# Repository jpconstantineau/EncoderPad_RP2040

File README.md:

# EncoderPad RP2040

### What is the EncoderPad RP2040?

The EncoderPad RP2040 is a Video Editing Macropad with a 60mm Encoder Wheel. This encoder is made of metal and feels like it will last forever. The EncoderPad uses 9 mechanical switches (Cherry MX type).  The keys are hot-swap socketed and have an individual underglow RGB LED which can be turned on.

### How do I build it?

You don't need many tools to build it!  
* Install the rotary encoder on the top plate. (there are nuts at the back)
* Press the switches through the top plate
* Align the key switch pins with their sockets and press them in, 
* Attach the wires for the rotary encoder
* Screw in the top/bottom screws through the standoffs
* Install the keycaps
* Install the adhesive rubber bump ons as feet.

### How do I program it?

The Encoder Pad can be programmed with CircuitPython.  To get started, get the latest download from the official [CircuitPython.org](https://circuitpython.org/) site, put the RP2040 in  booloader mode by pressing "reset" while pressing the "boot" button and drag/drop in the UF2 file you just downloaded. You are now ready to program it! No build tools required on your computer!

Notes: 
* CircuitPython is licensed under the [MIT License](https://github.com/adafruit/circuitpython/blob/main/LICENSE).
* Default Firmware for the EncoderPad is based on the [MACROPAD Hoykeys](https://learn.adafruit.com/macropad-hotkeys) example for the [Adafruit Macropad RP2040](https://learn.adafruit.com/adafruit-macropad-rp2040) which is part of the [Adafruit Learning System Guides](https://learn.adafruit.com/), licensed under the [MIT License](https://github.com/adafruit/Adafruit_Learning_System_Guides/blob/main/LICENSE).
* Default firmware is **MIT** licensed.

### Hardware License

Design of the EncoderPad_RP2040 is licensed under **CERN Open Hardware Licence Version 2 - Weakly Reciprocal**

See license.txt for more details. See this [FAQ](https://ohwr.org/project/cernohl/wikis/faq#q-copyright-does-not-cover-hardware-how-do-you-implement-strongly-reciprocal-licensing-in-cern-ohl-s) for more information on this license.

### Licenses from reference material and libraries

|  Item  | Description | Source  | License  |
|----|----      | :-----  | :-------- |
| RP2040 Hardware Design Guide  | RP2040 Documentation (for reference) | [link](https://datasheets.raspberrypi.org/rp2040/hardware-design-with-rp2040.pdf) | CC BY-ND |
| RP2040 Minimal Design Example | Kicad Project | [link](https://datasheets.raspberrypi.org/rp2040/Minimal-KiCAD.zip) | 3-Clause BSD (considered as source code included as part of documentation) |
| kicad libraries | Core libraries from Kicad | [link](https://www.kicad.org/libraries/license/) | CC-BY-SA 4.0 (with exception)|
| kicad libraries | switch symbols and footprints | [link](https://github.com/sszczep/kicad-libraries)| MIT | 

### openmoko-usb-oui application details

[USB PID Request](https://github.com/openmoko/openmoko-usb-oui)

1. (done) Have a README[.txt|.md] file describing which part is under which license this will help to quickly identify the project's license, particularly when several licenses are combined, or your are using libraries under other licenses. Also make sure the combination is allowed by the individual licenses.
2. (done) Include all full text licenses in a LICENSE[.txt] file
3. (done) Include a copyright notice in the schematic sheet(s), including author and date this will determine who the copyright holder is, and when the copyright will expire.
4. (done) Include the license name in the schematic sheet(s) this becomes important when different license are combined, and parts of the project, or libraries, are under different licenses
5. (done) Include all schematic symbols and board footprint libraries in the project without that the project can't be seen as complete. Also ensure their license is compatible.
66. (done) Export the schematic capture as pdf, and board layout as gerber+NC drill [and other fabrication output] files - not every user can, or wants, to install the EDA suite you are using. This is even more important if in the future this suite stops supporting the current format. If you don't want to mix the fabrication output with the source files, have a general project page pointing to the source files and fabrication output.

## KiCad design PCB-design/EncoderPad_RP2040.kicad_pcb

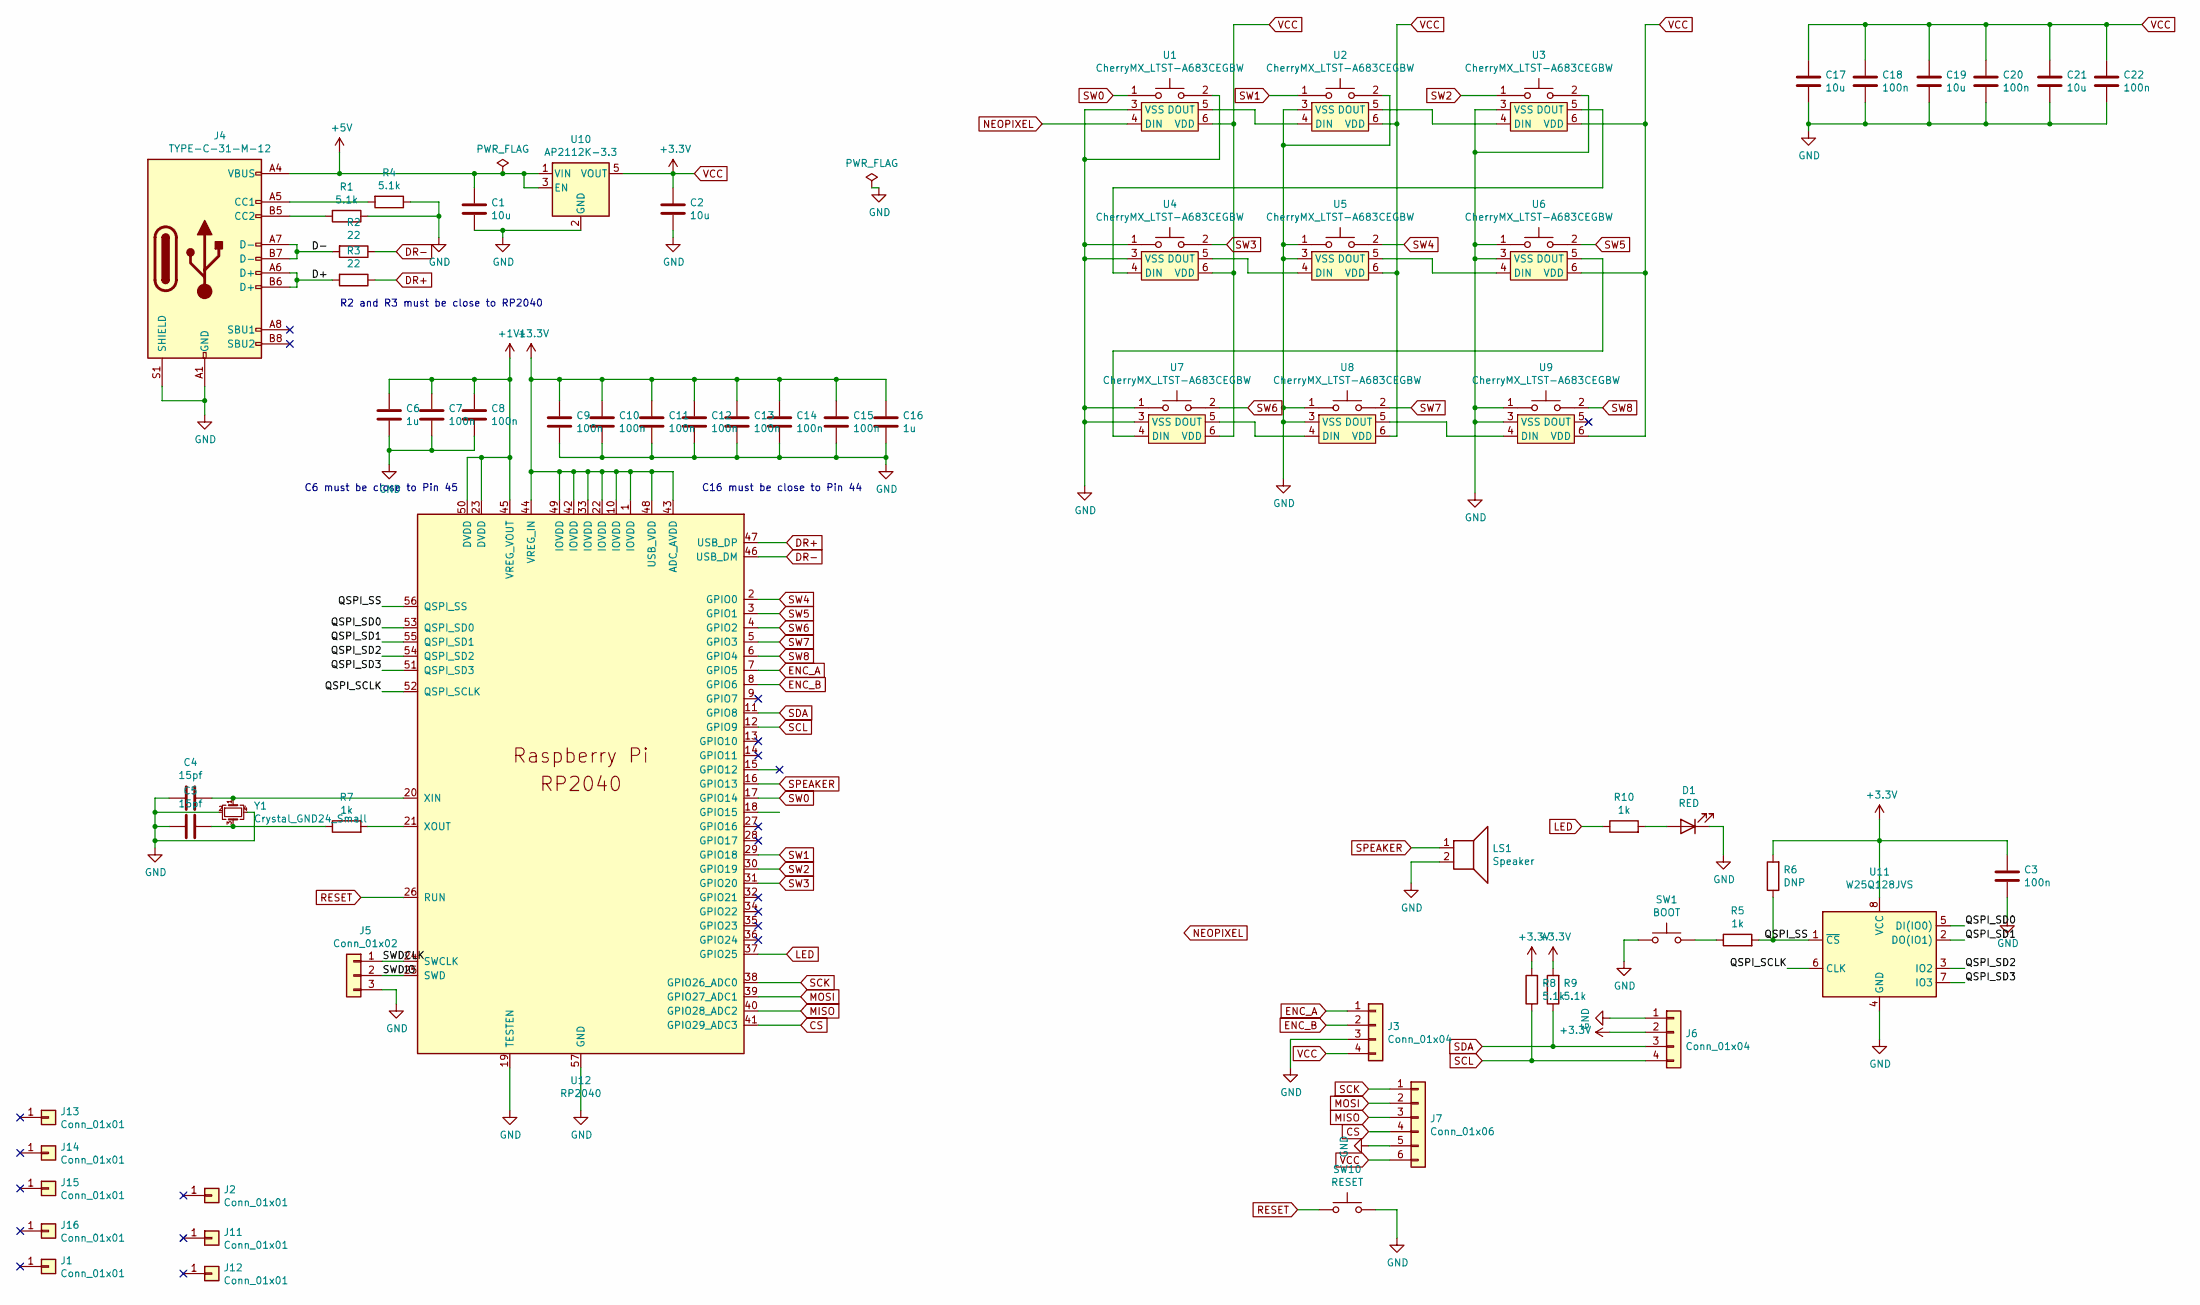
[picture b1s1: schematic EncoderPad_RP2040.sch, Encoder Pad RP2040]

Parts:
C1, C2, C17, C19, C21: 10u; C_0603_1608Metric; LCSC C15850
C3, C7, C8, C9, C10, C11, C12, C13, C14, C15, C18, C20, C22: 100n; C_0603_1608Metric; LCSC C14663
C4, C5: 15pf; C_0603_1608Metric; LCSC C1644
C6, C16: 1u; C_0603_1608Metric; LCSC C15849
D1: RED; LED_0603_1608Metric
J1: Conn_01x01; CNC_Encoder
J2, J11, J12, J13, J14, J15, J16: Conn_01x01; MountingHole_3.5mm
J3: Conn_01x04; PinHeader_1x04_P2.54mm_Horizontal
J4: TYPE-C-31-M-12; USB_C_Receptacle_HRO_TYPE-C-31-M-12; LCSC C165948
J5: Conn_01x02; PinHeader_1x03_P2.54mm_Vertical
J6: Conn_01x04; PinHeader_1x04_P2.54mm_Vertical
J7: Conn_01x06; PinHeader_1x06_P1.27mm_Vertical
LS1: Speaker; AST1109MLTRQ
R1, R4, R8, R9: 5.1k; R_0603_1608Metric; LCSC C23186
R2, R3: 22; R_0603_1608Metric; LCSC C23345
R5, R7, R10: 1k; R_0603_1608Metric; LCSC C21190
R6: DNP; R_0603_1608Metric
SW1: BOOT; SW_TACT_ALPS_SKQGABE010
SW10: RESET; SW_TACT_ALPS_SKQGABE010
U1, U2, U3, U4, U5, U6, U7, U8, U9: CherryMX_LTST-A683CEGBW; CherryMX_1.00u_PCB_KailhSocket_LTST-A683CEGBW-Rotated
U10: AP2112K-3.3; SOT-23-5
U11: W25Q128JVS; SOIC-8_5.23x5.23mm_P1.27mm; LCSC C97521
U12: RP2040; RP2040-QFN-56
Y1: Crystal_GND24_Small; Crystal_SMD_3225-4Pin_3.2x2.5mm; LCSC C97242

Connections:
+1V1: C6.1, C7.1, C8.1, U12.23 (DVDD), U12.45 (VREG_VOUT), U12.50 (DVDD)
+5V: C1.1, J4.A4 (VBUS), J4.A9 (VBUS), J4.B4 (VBUS), J4.B9 (VBUS), U10.1 (VIN), U10.3 (EN)
/D+: J4.A6 (D+), J4.B6 (D+), R3.2
/D-: J4.A7 (D-), J4.B7 (D-), R2.2
/QSPI_SCLK: U11.6 (CLK), U12.52 (QSPI_SCLK)
/QSPI_SD0: U11.5 (DI(IO0)), U12.53 (QSPI_SD0)
/QSPI_SD1: U11.2 (DO(IO1)), U12.55 (QSPI_SD1)
/QSPI_SD2: U11.3 (IO2), U12.54 (QSPI_SD2)
/QSPI_SD3: U11.7 (IO3), U12.51 (QSPI_SD3)
/QSPI_SS: R5.2, R6.1, U11.1 (~CS), U12.56 (QSPI_SS)
/SWDCLK: J5.1, U12.24 (SWCLK)
/SWDIO: J5.2, U12.25 (SWD)
CS: J7.4, U12.41 (GPIO29_ADC3)
DR+: R3.1, U12.47 (USB_DP)
DR-: R2.1, U12.46 (USB_DM)
ENC_A: J3.1, U12.7 (GPIO5)
ENC_B: J3.2, U12.8 (GPIO6)
GND: C1.2, C2.2, C3.2, C4.2, C5.2, C6.2, C7.2, C8.2, C9.2, C10.2, C11.2, C12.2, C13.2, C14.2, C15.2, C16.2, C17.2, C18.2, C19.2, C20.2, C21.2, C22.2, D1.1 (K), J3.3, J4.A1 (GND), J4.A12 (GND), J4.B1 (GND), J4.B12 (GND), J4.S1 (SHIELD), J5.3, J6.1, J7.5, LS1.2, R1.1, R4.1, SW1.1, SW10.2, U1.2, U1.3 (VSS), U2.2, U2.3 (VSS), U3.2, U3.3 (VSS), U4.1, U4.3 (VSS), U5.1, U5.3 (VSS), U6.1, U6.3 (VSS), U7.1, U7.3 (VSS), U8.1, U8.3 (VSS), U9.1, U9.3 (VSS), U10.2 (GND), U11.4 (GND), U12.19 (TESTEN), U12.57 (GND), Y1.2, Y1.4
LED: R10.1, U12.37 (GPIO25)
MISO: J7.3, U12.40 (GPIO28_ADC2)
MOSI: J7.2, U12.39 (GPIO27_ADC1)
NEOPIXEL: U1.4 (DIN), U12.18 (GPIO15)
unnamed: C4.1, U12.20 (XIN), Y1.1
unnamed: C5.1, R7.1, Y1.3
unnamed: D1.2 (A), R10.2
unnamed: J4.A5 (CC1), R4.2
unnamed: J4.B5 (CC2), R1.2
unnamed: R5.1, SW1.2
unnamed: R7.2, U12.21 (XOUT)
unnamed: U1.5 (DOUT), U2.4 (DIN)
unnamed: U2.5 (DOUT), U3.4 (DIN)
unnamed: U3.5 (DOUT), U4.4 (DIN)
unnamed: U4.5 (DOUT), U5.4 (DIN)
unnamed: U5.5 (DOUT), U6.4 (DIN)
unnamed: U6.5 (DOUT), U7.4 (DIN)
unnamed: U7.5 (DOUT), U8.4 (DIN)
unnamed: U8.5 (DOUT), U9.4 (DIN)
RESET: SW10.1, U12.26 (RUN)
SCK: J7.1, U12.38 (GPIO26_ADC0)
SCL: J6.4, R8.1, U12.12 (GPIO9)
SDA: J6.3, R9.1, U12.11 (GPIO8)
SPEAKER: LS1.1, U12.16 (GPIO13)
SW0: U1.1, U12.17 (GPIO14)
SW1: U2.1, U12.29 (GPIO18)
SW2: U3.1, U12.30 (GPIO19)
SW3: U4.2, U12.31 (GPIO20)
SW4: U5.2, U12.2 (GPIO0)
SW5: U6.2, U12.3 (GPIO1)
SW6: U7.2, U12.4 (GPIO2)
SW7: U8.2, U12.5 (GPIO3)
SW8: U9.2, U12.6 (GPIO4)
VCC: C2.1, C3.1, C9.1, C10.1, C11.1, C12.1, C13.1, C14.1, C15.1, C16.1, C17.1, C18.1, C19.1, C20.1, C21.1, C22.1, J3.4, J6.2, J7.6, R6.2, R8.2, R9.2, U1.6 (VDD), U2.6 (VDD), U3.6 (VDD), U4.6 (VDD), U5.6 (VDD), U6.6 (VDD), U7.6 (VDD), U8.6 (VDD), U9.6 (VDD), U10.5 (VOUT), U11.8 (VCC), U12.1 (IOVDD), U12.10 (IOVDD), U12.22 (IOVDD), U12.33 (IOVDD), U12.42 (IOVDD), U12.43 (ADC_AVDD), U12.44 (VREG_IN), U12.48 (USB_VDD), U12.49 (IOVDD)

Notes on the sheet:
R2 and R3 must be close to RP2040
C6 must be close to Pin 45
C16 must be close to Pin 44

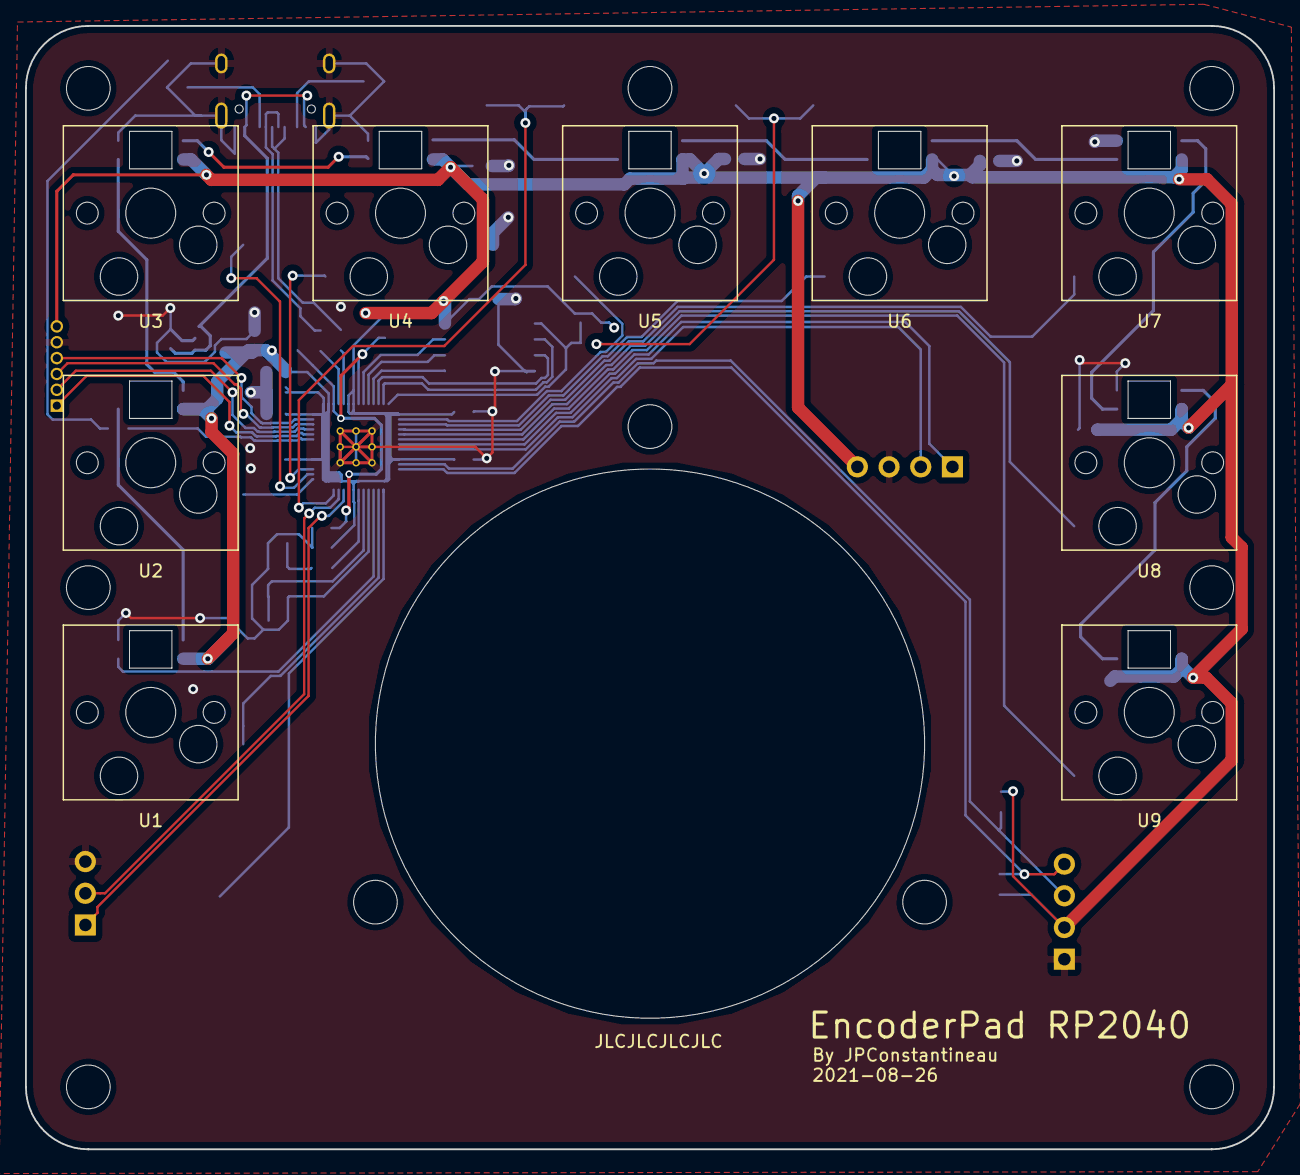
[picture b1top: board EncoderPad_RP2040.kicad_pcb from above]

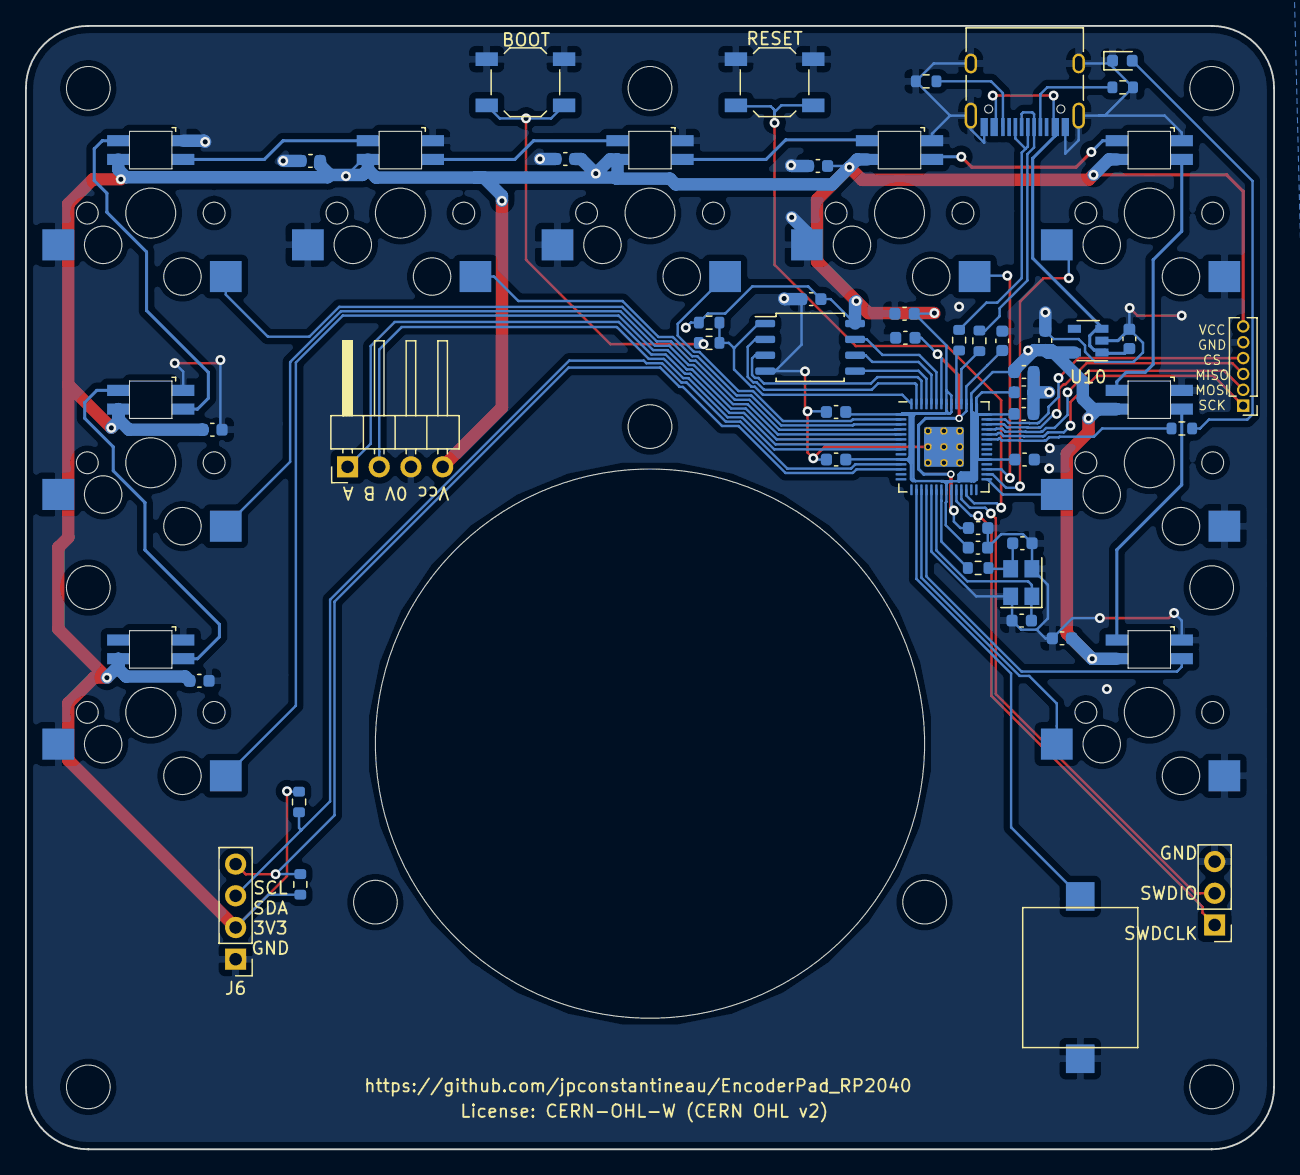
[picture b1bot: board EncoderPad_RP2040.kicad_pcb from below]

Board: 2 copper layers, 100.0 x 90.0 mm, 62 parts (45 on the bottom side), 52 nets.

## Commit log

2021-08-27 updated readme - firmware license
2021-08-27 added WIP prototype firmware
2021-08-27 updated code.py
2021-09-20 added HtmlBOM
2021-10-29 adding BOM - closes #1

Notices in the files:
PCB-design/EncoderPad_RP2040.kicad_pcb:
License: CERN-OHL-W (CERN OHL v2)
